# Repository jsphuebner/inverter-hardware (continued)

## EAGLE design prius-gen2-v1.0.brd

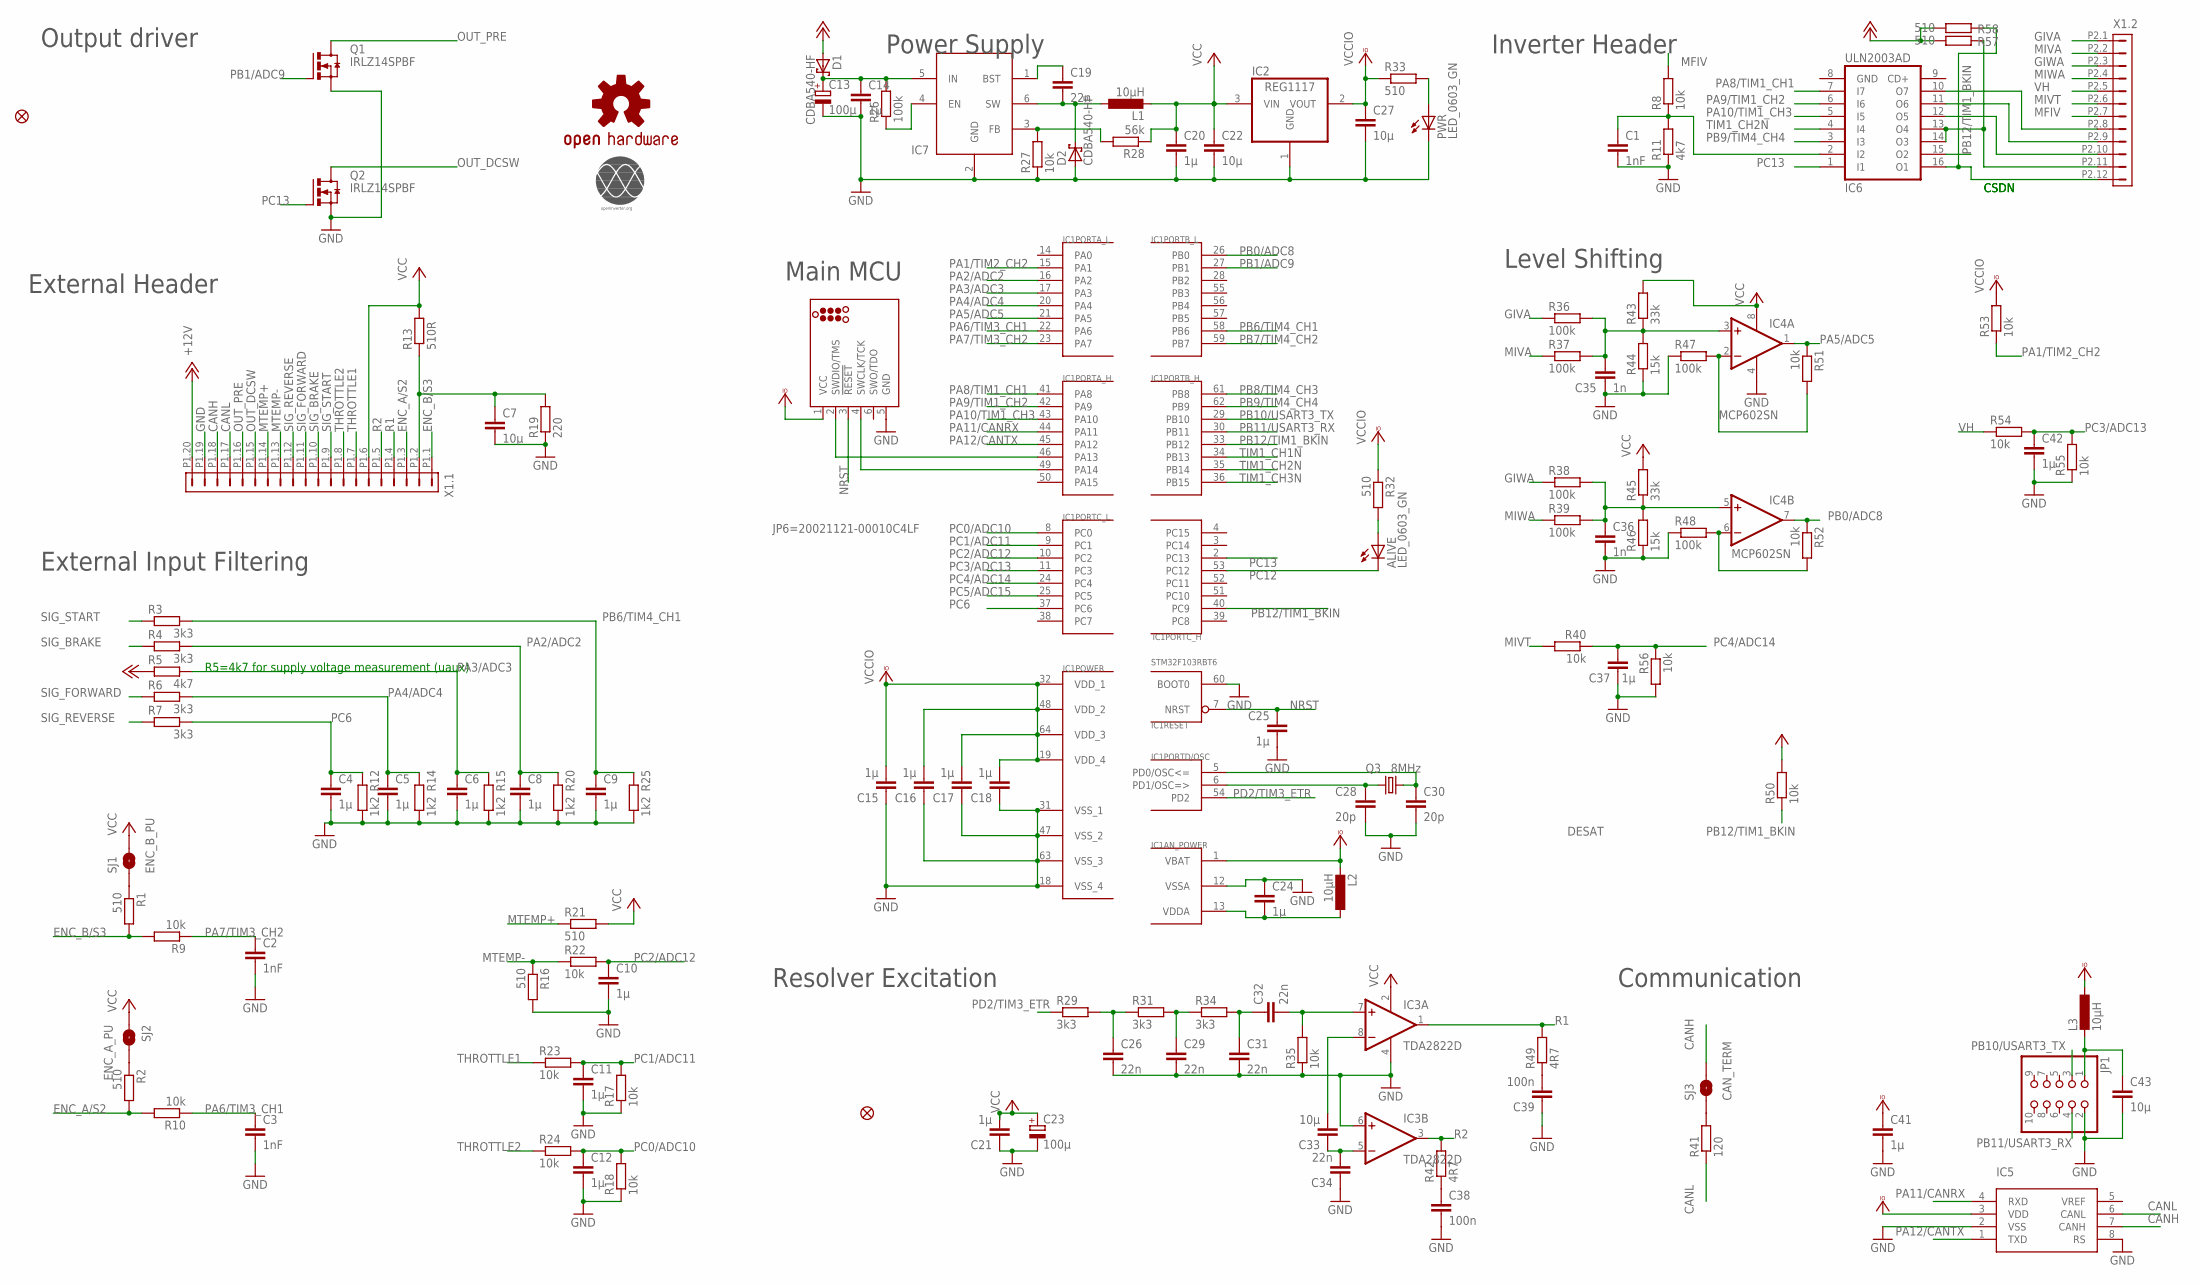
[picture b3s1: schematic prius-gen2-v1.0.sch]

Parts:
ALIVE: LED_0603_GN; SML0805
C1, C2, C3: 1nF; C0603
C4, C5, C6, C8, C9, C10, C11, C12, C14, C15, C16, C17, C18, C20, C21, C24, C25, C37, C41, C42: 1µ; C0603
C7, C22, C27, C33, C43: 10µ; C0805
C13, C23: 100µ; UD-6,3X7,7_NICHICON
C19, C26, C29, C31, C32, C34: 22n; C0603
C28, C30: 20p; C0603
C35, C36: 1n; C0603
C38, C39: 100n; C0603
D1, D2: CDBA540-HF; SMB
FID1, FID2: FIDUCIAL1X2.5; FIDUCIAL-1X2.5
IC1: STM32F103RBT6; TQFP64
IC2: REG1117; SOT223
IC3: TDA2822D; SO08
IC4: MCP602SN; SO08
IC5: SN65HVD230; SO08
IC6: ULN2003AD; SO16
IC7: MB2359DJ; SOT23-6
J1: TC2030_SWD-MCP; TC2030-MCP
JP1: PINHD-2X5/90; 2X05/90
L1: 10µH; L2825P
L2, L3: 10µH; L2012C
LOGO1: OSHW-LOGOM; OSHW-LOGO-M
PWR: LED_0603_GN; SML0805
Q1, Q2: IRLZ14SPBF; D-PAK_TO252AA
Q3: 8MHz; CRYSTAL-TXC-7A
R1, R2, R16, R21, R32, R33, R57, R58: 510; R0603
R3, R4, R6, R7, R29, R31, R34: 3k3; R0603
R5, R11: 4k7; R0603
R8, R9, R10, R17, R18, R22, R23, R24, R27, R35, R40, R50, R51, R52, R53, R54, R55, R56: 10k; R0603
R12, R14, R15, R20, R25: 1k2; R0603
R13: 510R; R0603
R19: 220; R0603
R26, R36, R37, R38, R39, R47, R48: 100k; R0603
R28: 56k; R0603
R41: 120; R0603
R42, R49: 4R7; R0603
R43, R45: 33k; R0603
R44, R46: 15k; R0603
SJ1: ENC_B_PU; SJ_2S-NO
SJ2: ENC_A_PU; SJ_2S-NO
SJ3: CAN_TERM; SJ_2S-NO
U$1: OI-LOGO; OI_LOGO
X1: 5810132011

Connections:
+12V: D1.A, R5.1, R57.1, R58.1, X1.P1.20 (20)
CANH: IC5.7 (CANH), SJ3.2, X1.P1.18 (18)
CANL: IC5.6 (CANL), R41.1, X1.P1.17 (17)
ENC_A/S2: R2.2, R10.2, X1.P1.3 (3)
ENC_B/S3: R1.2, R9.2, X1.P1.1 (1)
GIVA: R36.1, X1.P2.1 (1)
GIWA: R38.1, X1.P2.3 (3)
GND: C1.2, C2.2, C3.2, C4.2, C5.2, C6.2, C7.2, C8.2, C9.2, C10.2, C11.2, C12.2, C13.-, C14.2, C15.1, C16.1, C17.1, C18.1, C20.2, C21.1, C22.2, C23.-, C24.1, C25.2, C26.2, C27.2, C28.2, C29.2, C30.2, C31.2, C34.1, C35.2, C36.2, C37.2, C38.2, C39.1, C41.2, C42.2, C43.2, D2.A, IC1.12 (VSSA), IC1.18 (VSS_4), IC1.31 (VSS_1), IC1.47 (VSS_2), IC1.60 (BOOT0), IC1.63 (VSS_3), IC2.1 (GND), IC3.4 (V-), IC3.6 (+IN), IC4.4 (V-), IC5.2 (VSS), IC5.8 (RS), IC6.8 (GND), IC7.2 (GND), J1.5 (GND), JP1.2, PWR.C, Q1.3 (S), Q2.3 (S), R11.1, R12.1, R14.1, R15.1, R16.2, R17.1, R18.1, R19.1, R20.1, R25.1, R27.1, R35.1, R44.1, R46.1, R47.1, R48.1, R55.1, R56.2, X1.P1.19 (19)
MFIV: R8.2, X1.P2.7 (7)
MIVA: R37.1, X1.P2.2 (2)
MIVT: R40.2, X1.P2.6 (6)
MIWA: R39.1, X1.P2.4 (4)
MTEMP+: R21.1, X1.P1.14 (14)
MTEMP-: R16.1, R22.1, X1.P1.13 (13)
unnamed: IC6.12 (O5), X1.P2.10 (10)
unnamed: C28.1, IC1.6 (PD1/OSC=>), Q3.P$1 (1)
unnamed: C13.+, C14.1, D1.C, IC7.5 (IN), R26.2
unnamed: C30.1, IC1.5 (PD0/OSC<=), Q3.P$2 (2)
unnamed: C19.1, IC7.1 (BST)
unnamed: IC1.46 (PA13), J1.2 (SWDIO/TMS)
unnamed: C24.2, IC1.13 (VDDA), L2.1
unnamed: IC7.4 (EN), R26.1
unnamed: IC1.49 (PA14), J1.4 (SWCLK/TCK)
unnamed: C33.1, C34.2, IC3.5 (-IN)
unnamed: C39.2, R49.1
unnamed: C33.2, IC3.8 (-IN)
unnamed: IC7.3 (FB), R27.2, R28.2
unnamed: C19.2, D2.C, IC7.6 (SW), L1.1
unnamed: IC6.11 (O6), X1.P2.9 (9)
unnamed: IC6.10 (O7), X1.P2.8 (8)
unnamed: C29.1, R31.2, R34.1
unnamed: C31.1, C32.1, R34.2
unnamed: C32.2, IC3.7 (+IN), R35.2
unnamed: R2.1, SJ2.2
unnamed: R1.1, SJ1.1
unnamed: PWR.A, R33.2
unnamed: ALIVE.A, R32.2
unnamed: C1.1, IC6.2 (I2), R8.1, R11.2
unnamed: IC6.16 (O1), R58.2, X1.P2.12 (12)
unnamed: R41.2, SJ3.1
unnamed: C38.1, R42.1
unnamed: C43.1, JP1.1, L3.2
unnamed: IC6.13 (O4), IC6.14 (O3), R57.2, X1.P2.11 (11)
unnamed: C26.1, R29.2, R31.1
unnamed: C36.1, IC4.5 (+IN), R38.2, R39.2, R45.1, R46.2
unnamed: C35.1, IC4.3 (+IN), R36.2, R37.2, R43.1, R44.2
unnamed: IC4.2 (-IN), R47.2, R51.2
unnamed: IC4.6 (-IN), R48.2, R52.2
NRST: C25.1, IC1.7 (NRST), J1.3 (!RESET)
OUT_DCSW: Q2.4 (D), X1.P1.15 (15)
OUT_PRE: Q1.4 (D), X1.P1.16 (16)
PA1/TIM2_CH2: IC1.15 (PA1), R53.1
PA2/ADC2: C8.1, IC1.16 (PA2), R4.2, R20.2
PA3/ADC3: C6.1, IC1.17 (PA3), R5.2, R15.2
PA4/ADC4: C5.1, IC1.20 (PA4), R6.2, R14.2
PA5/ADC5: IC1.21 (PA5), IC4.1 (OUT), R51.1
PA6/TIM3_CH1: C3.1, IC1.22 (PA6), R10.1
PA7/TIM3_CH2: C2.1, IC1.23 (PA7), R9.1
PA8/TIM1_CH1: IC1.41 (PA8), IC6.7 (I7)
PA9/TIM1_CH2: IC1.42 (PA9), IC6.6 (I6)
PA10/TIM1_CH3: IC1.43 (PA10), IC6.5 (I5)
PA11/CANRX: IC1.44 (PA11), IC5.4 (RXD)
PA12/CANTX: IC1.45 (PA12), IC5.1 (TXD)
PB0/ADC8: IC1.26 (PB0), IC4.7 (OUT), R52.1
PB1/ADC9: IC1.27 (PB1), Q1.1 (G)
PB6/TIM4_CH1: C9.1, IC1.58 (PB6), R3.2, R25.2
PB7/TIM4_CH2: IC1.59 (PB7)
PB8/TIM4_CH3: IC1.61 (PB8)
PB9/TIM4_CH4: IC1.62 (PB9), IC6.3 (I3)
PB10/USART3_TX: IC1.29 (PB10), JP1.3
PB11/USART3_RX: IC1.30 (PB11), JP1.4
PB12/TIM1_BKIN: IC1.33 (PB12), IC1.40 (PC9), IC6.15 (O2), R50.1
PC0/ADC10: C12.1, IC1.8 (PC0), R18.2, R24.2
PC1/ADC11: C11.1, IC1.9 (PC1), R17.2, R23.2
PC2/ADC12: C10.1, IC1.10 (PC2), R22.2
PC3/ADC13: C42.1, IC1.11 (PC3), R54.2, R55.2
PC4/ADC14: C37.1, IC1.24 (PC4), R40.1, R56.1
PC5/ADC15: IC1.25 (PC5)
PC6: C4.1, IC1.37 (PC6), R7.2, R12.2
PC12: ALIVE.C, IC1.53 (PC12)
PC13: IC1.2 (PC13), IC6.1 (I1), Q2.1 (G)
PD2/TIM3_ETR: IC1.54 (PD2), R29.1
R1: IC3.1 (OUT), R49.2, X1.P1.4 (4)
R2: IC3.3 (OUT), R42.2, X1.P1.5 (5)
S4/S1: C7.1, R13.1, R19.2, X1.P1.2 (2)
SIG_BRAKE: R4.1, X1.P1.10 (10)
SIG_FORWARD: R6.1, X1.P1.11 (11)
SIG_REVERSE: R7.1, X1.P1.12 (12)
SIG_START: R3.1, X1.P1.9 (9)
THROTTLE1: R23.1, X1.P1.7 (7)
THROTTLE2: R24.1, X1.P1.8 (8)
TIM1_CH1N: IC1.34 (PB13)
TIM1_CH2N: IC1.35 (PB14), IC6.4 (I4)
TIM1_CH3N: IC1.36 (PB15)
VCC: C20.1, C21.2, C22.1, C23.+, IC2.3 (VIN), IC3.2 (V+), IC4.8 (V+), L1.2, R13.2, R21.2, R28.1, R43.2, R45.2, R50.2, SJ1.2, SJ2.1, X1.P1.6 (6)
VCCIO: C15.2, C16.2, C17.2, C18.2, C27.1, C41.1, IC1.1 (VBAT), IC1.19 (VDD_4), IC1.32 (VDD_1), IC1.48 (VDD_2), IC1.64 (VDD_3), IC2.2 (VOUT), IC5.3 (VDD), J1.1 (VCC), L2.2, L3.1, R32.1, R33.1, R53.2
VH: R54.1, X1.P2.5 (5)

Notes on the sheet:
Output driver
Resolver Excitation
External Input Filtering
External Header
Communication
Power Supply
Inverter Header
Level Shifting
Main MCU
R5=4k7 for supply voltage measurement (uaux)
JP6=20021121-00010C4LF
DESAT
IC7
IC5
CSDN

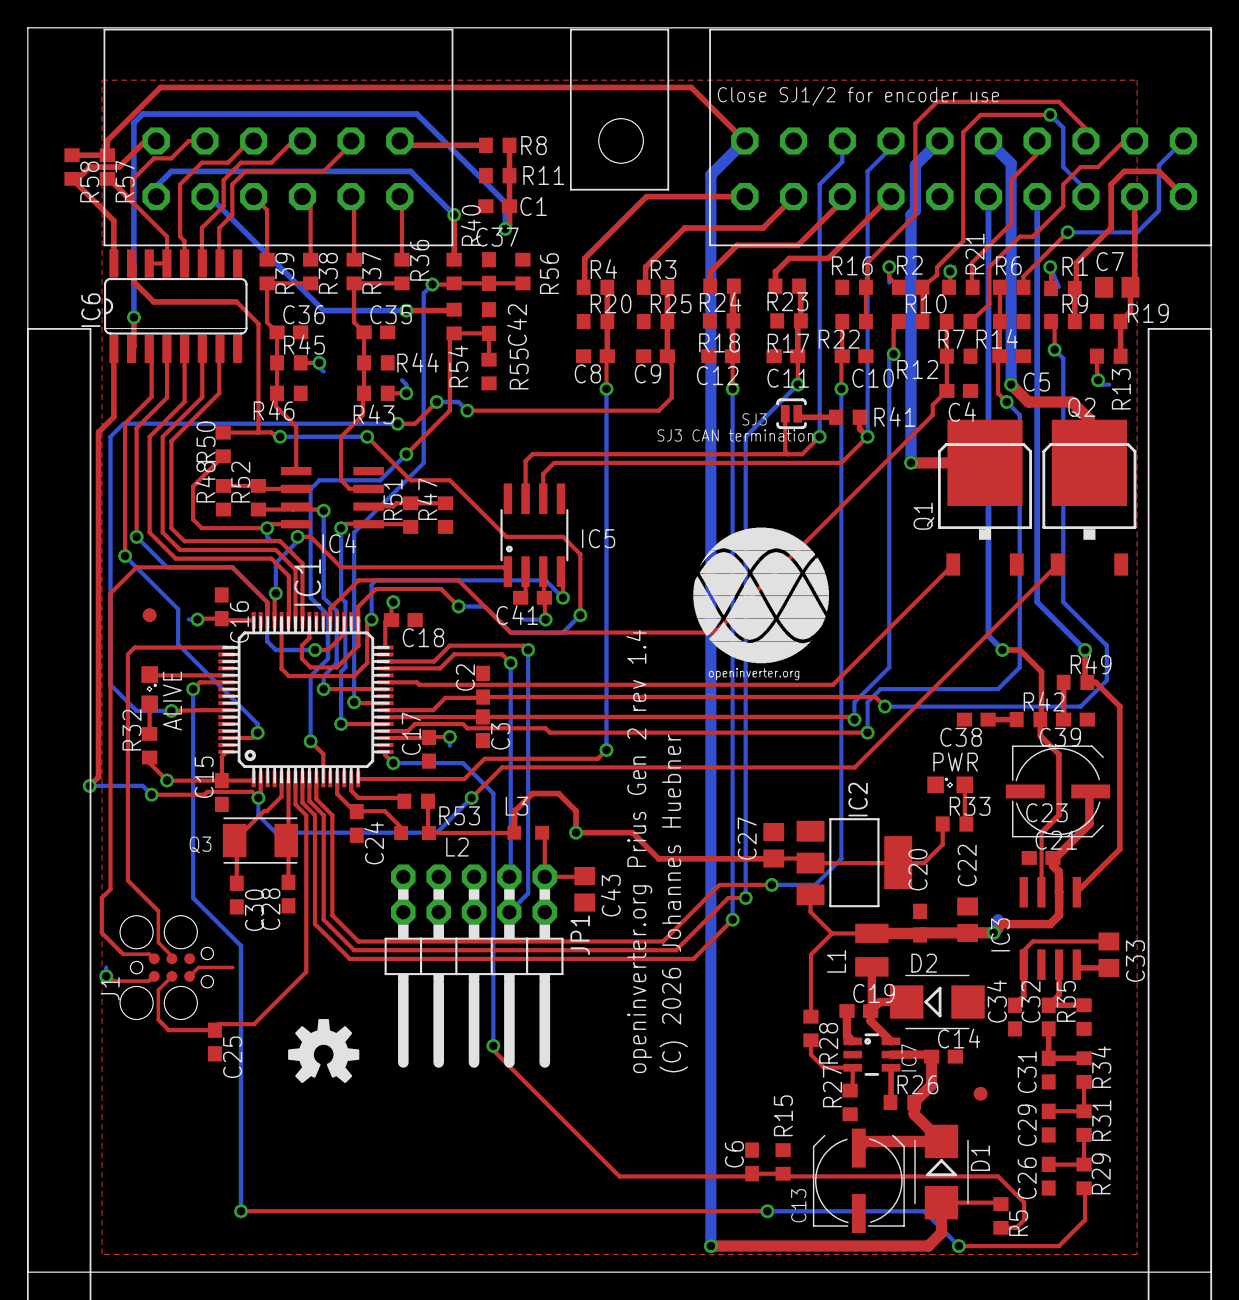
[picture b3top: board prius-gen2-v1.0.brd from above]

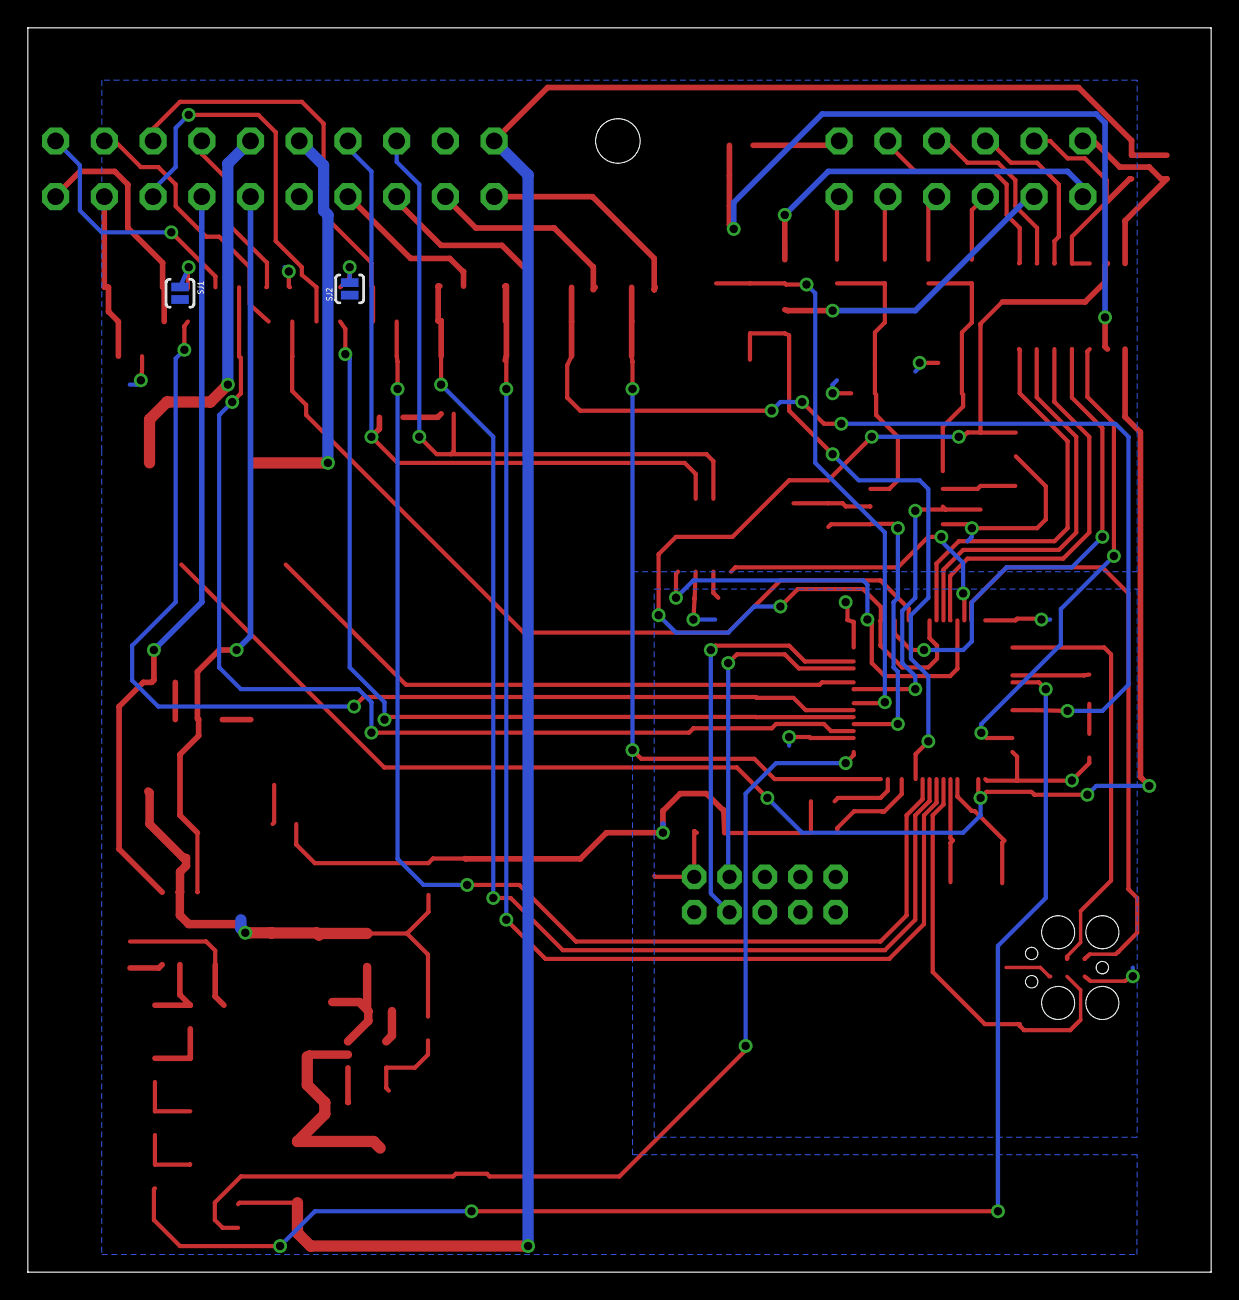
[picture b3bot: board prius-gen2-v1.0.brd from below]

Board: 2 copper layers, 85.0 x 89.4 mm, 126 parts (2 on the bottom side), 92 nets.

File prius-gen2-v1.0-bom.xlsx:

Designator | Comment | Package | LCSC Part #
ALIVE, PWR | LED_0603_GN | CHIPLED-0805 | C84256
C7, C22, C27, C33, C43 | 10uF | C0805 | C15850
C1, C2, C3, C35, C36 | 1nF | C0603 | C46653
C13, C23 | 100uF | SMD-ECAP-6.3X7.7 | C176675 | e
C28, C30 | 22p | C0603 | C1804
C4, C5, C6, C8, C9, C10, C11, C12, C14, C15, C16, C17, C18, C20, C21, C24, C25,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 | 1uF | C0603 | C28323
C19, C26, C29, C31, C32, C34 | 22n | C0603 | C21122
D1, D2 | CDBA540-HF | SMB | C22452
IC7 | MP2359DJ-LF-Z | TSOT-23-6 | C14259
IC3 | TDA2822D | SO08 | C73296 | e
IC5 | SN65HVD230 | SO08 | C12084
IC1 | STM32F103RBT6 | LQFP-64_10.0x10.0x0.5P | C8735
IC6 | ULN2003AD | SO16 | C7512
IC4 | MCP6002T-I/SN | SO08 | C7377
IC2 | AMS1117-3.3 | SOT-223 | C6186
L2, L3 | 10uH | L0805 | C1046
L1 | 6.8uH | L1210 | C87559 | e
Q3 | 8MHz | SMD-5032_2P | C115962
R19 | 220Ω | R0603 | C22962
R12, R14, R15, R20, R25 | 1.2KΩ | R0603 | C22765
R1, R2, R13, R16, R21, R32, R33 | 510Ω | R0603 | C23193
R8, R9, R10, R17, R18, R22, R23, R24, R27, R30, R35, R40, R50, R51, R52, R53, R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 | 10KΩ | R0603 | C17414
R3, R4, R6, R7, R29, R31, R34 | 3.3KΩ | R0603 | C26010
R5, R11 | 4.7KΩ | R0603 | C17673
R42, R49 | 4.7Ω | R0603 | C23164
R26, R36, R37, R38, R39, R47, R48 | 100kΩ | R0603 | C25803
R28 | 56kΩ | R0603 | C23206
Q1, Q2 | AP9T18GH-HF | TO-252-2 | C124546 | e
C38, C39 | 100nF | C0603 | C14663
R44, R46 | 15kΩ | R0603 | C22809
R43, R45 | 33kΩ | R0603 | C4216
R41 | 120Ω | R0603 | C22787

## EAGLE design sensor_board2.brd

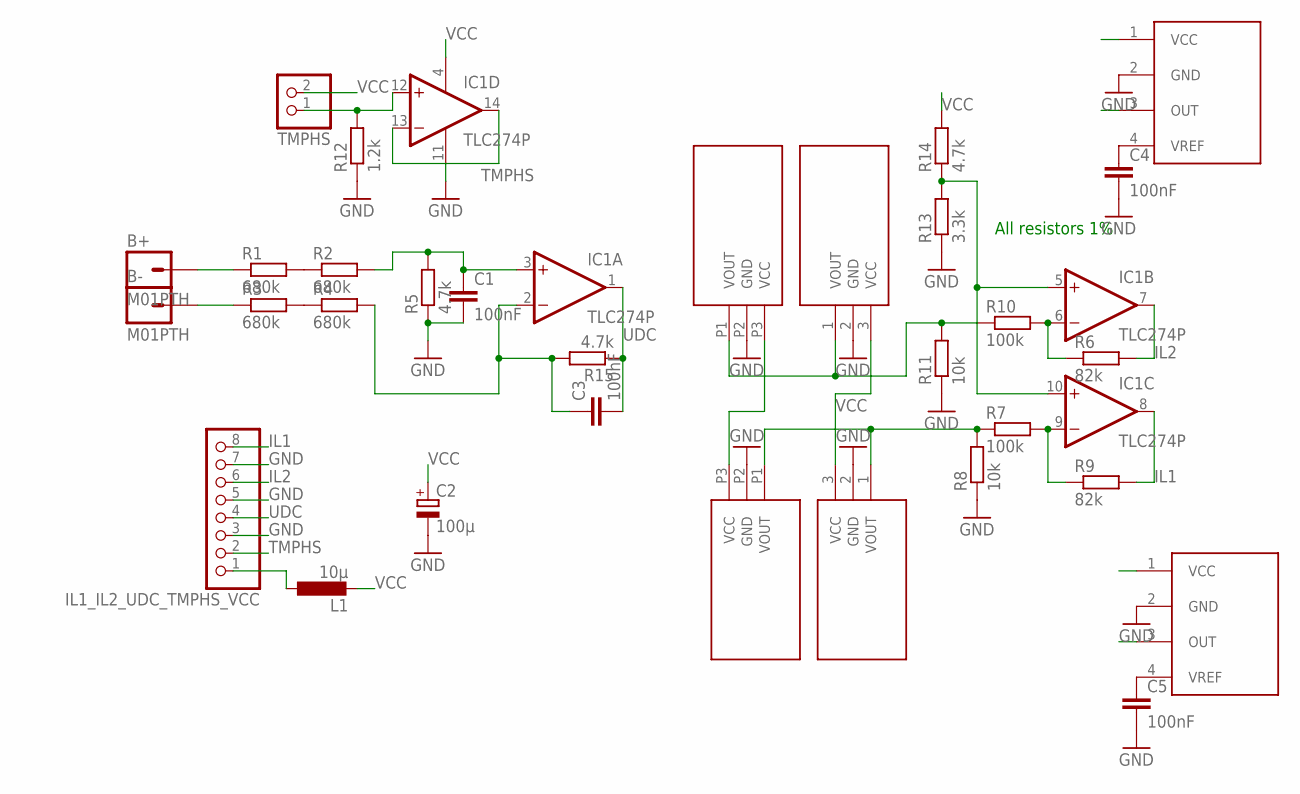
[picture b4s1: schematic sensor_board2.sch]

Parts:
B+: M01PTH; 1X01
B-: M01PTH; 1X01
C1, C3, C4, C5: 100nF; C025-024X044
C2: 100µ; E2,5-6E
IC1: TLC274P; DIL14
IL1_IL2_UDC_TMPHS_VCC: PINHD-1X8; 1X08
L1: 10µ; 0207/12
R1, R2, R3, R4: 680k; 0207/10
R5, R14, R15: 4.7k; 0207/10
R6, R9: 82k; 0207/10
R7, R10: 100k; 0207/10
R8, R11: 10k; 0207/10
R12: 1.2k; 0207/10
R13: 3.3k; 0207/10
TMPHS: PINHD-1X2; 1X02
U$1, U$2: TAMURA_L01Z_S05
U$3, U$4: HTFS
U$5, U$6: TAMURA_L06P_S05L06P; TAMURA_L06P_S05

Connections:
GND: C1.2, C2.-, C4.2, C5.2, IC1.11 (V-), IL1_IL2_UDC_TMPHS_VCC.3, IL1_IL2_UDC_TMPHS_VCC.5, IL1_IL2_UDC_TMPHS_VCC.7, R5.1, R8.1, R11.1, R12.1, R13.1, U$1.2 (GND), U$2.2 (GND), U$3.2 (GND), U$4.2 (GND), U$5.P2 (GND), U$6.P2 (GND)
IL1: IC1.8 (OUT), IL1_IL2_UDC_TMPHS_VCC.8, R9.2
IL2: IC1.7 (OUT), IL1_IL2_UDC_TMPHS_VCC.6, R6.2
unnamed: R1.2, R2.1
unnamed: R3.2, R4.1
unnamed: IC1.5 (+IN), IC1.10 (+IN), R13.2, R14.1
unnamed: C1.1, IC1.3 (+IN), R2.2, R5.2
unnamed: B+.1, R1.1
unnamed: B-.1, R3.1
unnamed: IL1_IL2_UDC_TMPHS_VCC.1, L1.1
unnamed: IC1.9 (-IN), R7.2, R9.1
unnamed: IC1.6 (-IN), R6.1, R10.2
unnamed: C3.1, IC1.2 (-IN), R4.2, R15.2
unnamed: C4.1, U$3.4 (VREF)
unnamed: C5.1, U$4.4 (VREF)
unnamed: IC1.12 (+IN), R12.2, TMPHS.1
TMPHS: IC1.13 (-IN), IC1.14 (OUT), IL1_IL2_UDC_TMPHS_VCC.2
UDC: C3.2, IC1.1 (OUT), IL1_IL2_UDC_TMPHS_VCC.4, R15.1
VCC: C2.+, IC1.4 (V+), L1.2, R14.2, TMPHS.2, U$1.3 (VCC), U$2.3 (VCC), U$3.1 (VCC), U$4.1 (VCC), U$5.P3 (VCC), U$6.P3 (VCC)
VOUT1: R7.1, R8.2, U$2.1 (VOUT), U$4.3 (OUT), U$6.P1 (VOUT)
VOUT2: R10.1, R11.2, U$1.1 (VOUT), U$3.3 (OUT), U$5.P1 (VOUT)

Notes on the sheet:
All resistors 1%

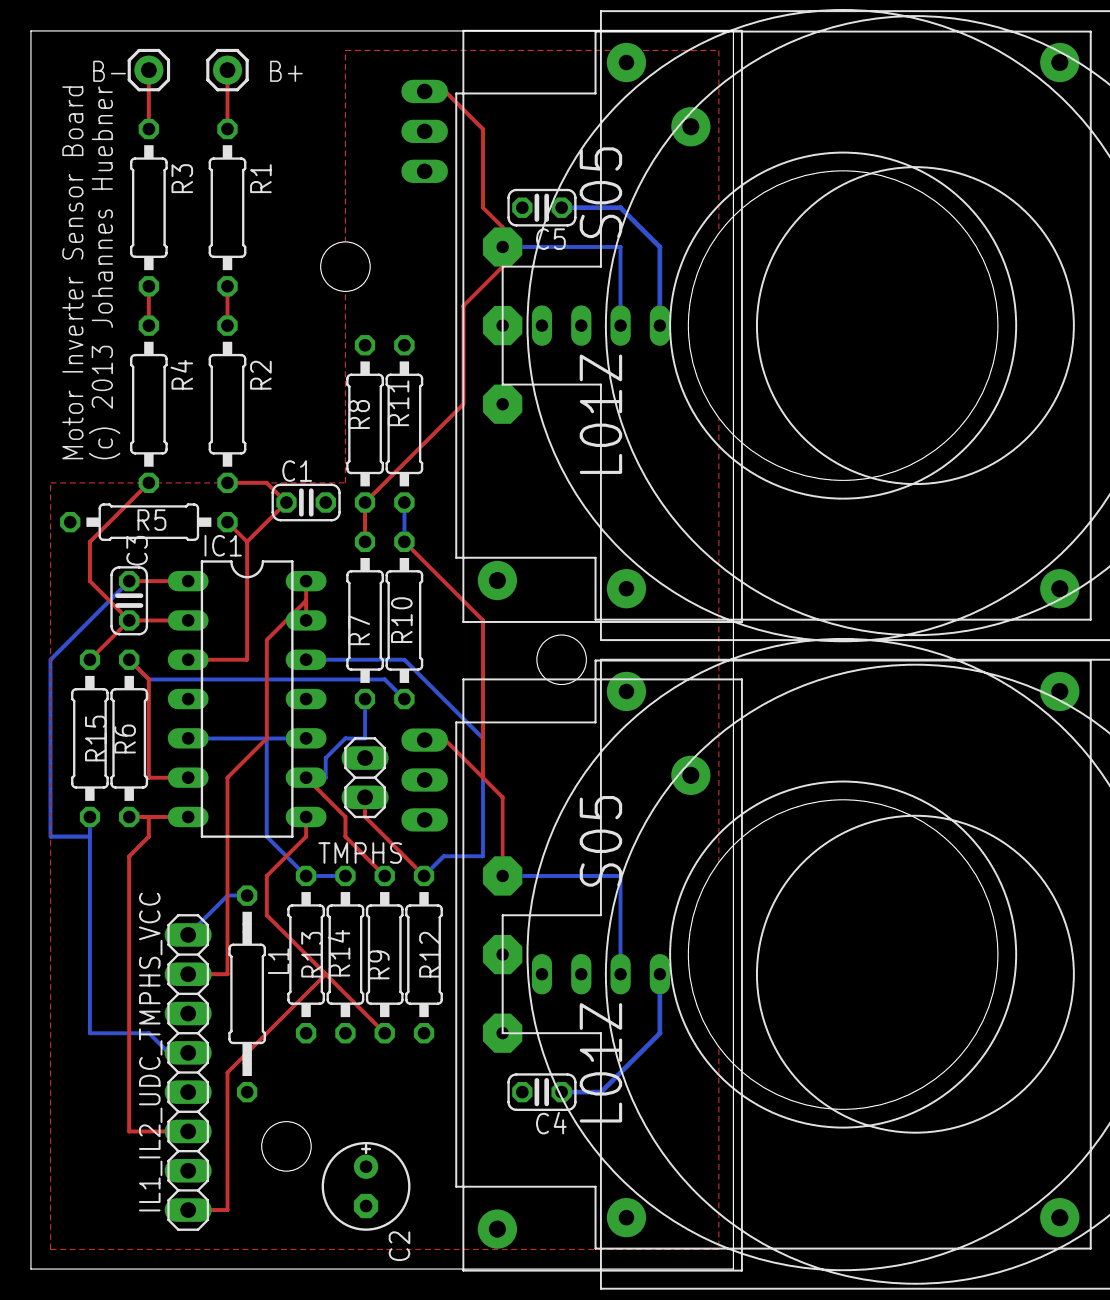
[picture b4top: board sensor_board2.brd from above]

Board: 2 copper layers, 45.4 x 80.0 mm, 32 parts (0 on the bottom side), 21 nets.

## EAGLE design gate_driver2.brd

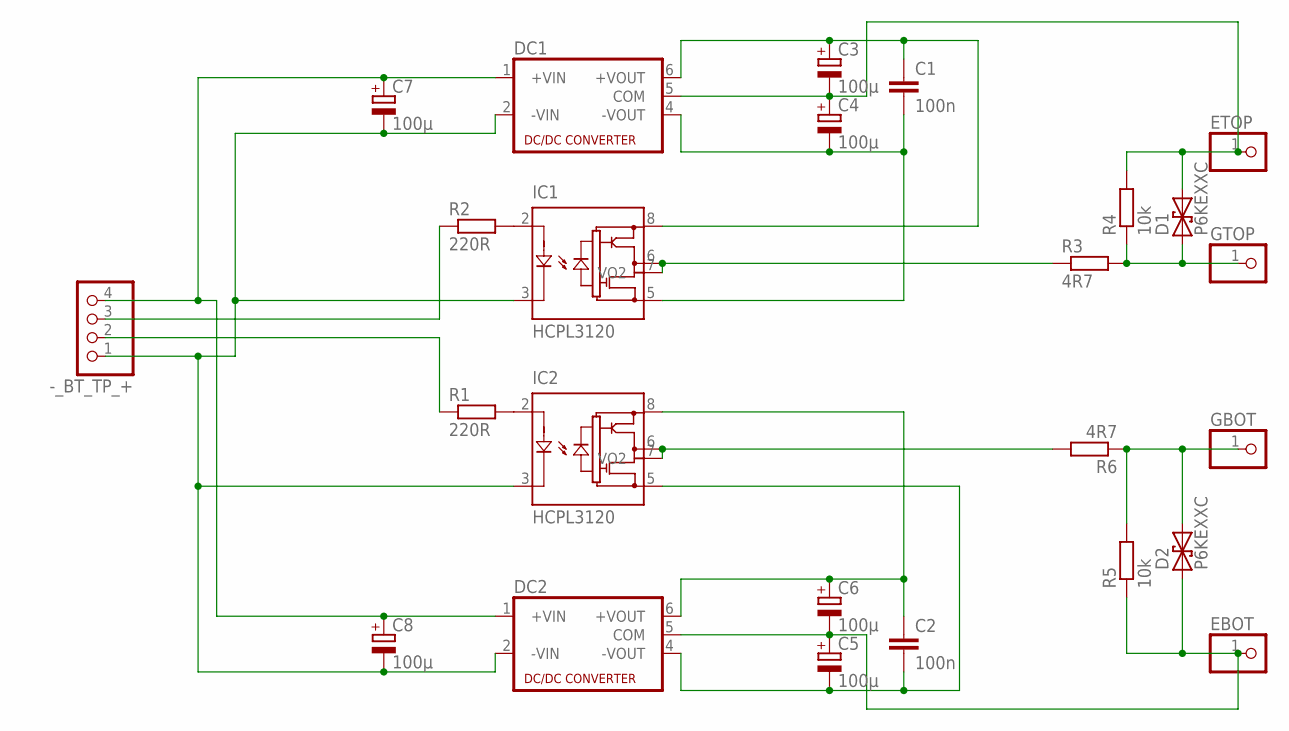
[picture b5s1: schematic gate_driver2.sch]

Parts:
-_BT_TP_+: PINHD-1X4; 1X04
C1, C2: 100n; C050-025X075
C3, C4, C5, C6: 100µ; E2,5-6E
C7, C8: 100µ; E2,5-5
D1, D2: P6KEXXC; CB417-15
DC1, DC2: NMA
EBOT: PINHD-1X1; 1X01
ETOP: PINHD-1X1; 1X01
GBOT: PINHD-1X1; 1X01
GTOP: PINHD-1X1; 1X01
IC1, IC2: HCPL3120; DIL08
R1, R2: 220R; 0207/10
R3, R6: 4R7; 0309/12
R4, R5: 10k; 0207/10

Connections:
EBOT: C5.+, C6.-, D2.A (1), DC2.5 (COM), EBOT.1, R5.1
ETOP: C3.-, C4.+, D1.C (2), DC1.5 (COM), ETOP.1, R4.2
GBOT: D2.C (2), GBOT.1, R5.2, R6.1
GND: -_BT_TP_+.1, C7.-, C8.-, DC1.2 (-VIN), DC2.2 (-VIN), IC1.3 (CATHODE), IC2.3 (CATHODE)
GTOP: D1.A (1), GTOP.1, R3.2, R4.1
unnamed: IC2.2 (ANODE), R1.2
unnamed: IC1.2 (ANODE), R2.2
unnamed: C1.2, C4.-, DC1.4 (-VOUT), IC1.5 (VEE)
unnamed: C1.1, C3.+, DC1.6 (+VOUT), IC1.8 (VCC)
unnamed: C2.1, C6.+, DC2.6 (+VOUT), IC2.8 (VCC)
unnamed: C2.2, C5.-, DC2.4 (-VOUT), IC2.5 (VEE)
unnamed: IC1.6 (VO), IC1.7 (VO2), R3.1
unnamed: IC2.6 (VO), IC2.7 (VO2), R6.2
unnamed: -_BT_TP_+.4, C7.+, C8.+, DC1.1 (+VIN), DC2.1 (+VIN)
unnamed: -_BT_TP_+.3, R2.1
unnamed: -_BT_TP_+.2, R1.1

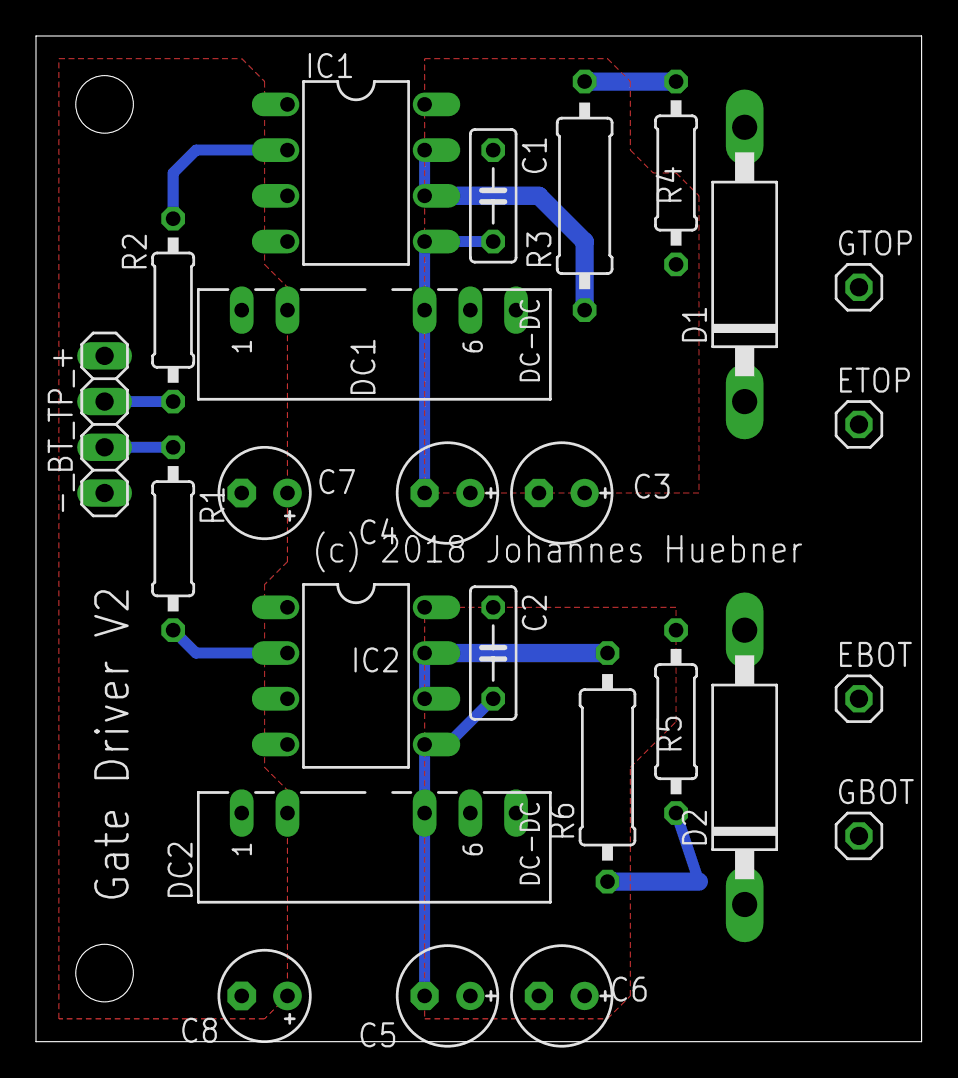
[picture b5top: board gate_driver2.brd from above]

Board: 2 copper layers, 49.2 x 55.9 mm, 25 parts (0 on the bottom side), 16 nets.

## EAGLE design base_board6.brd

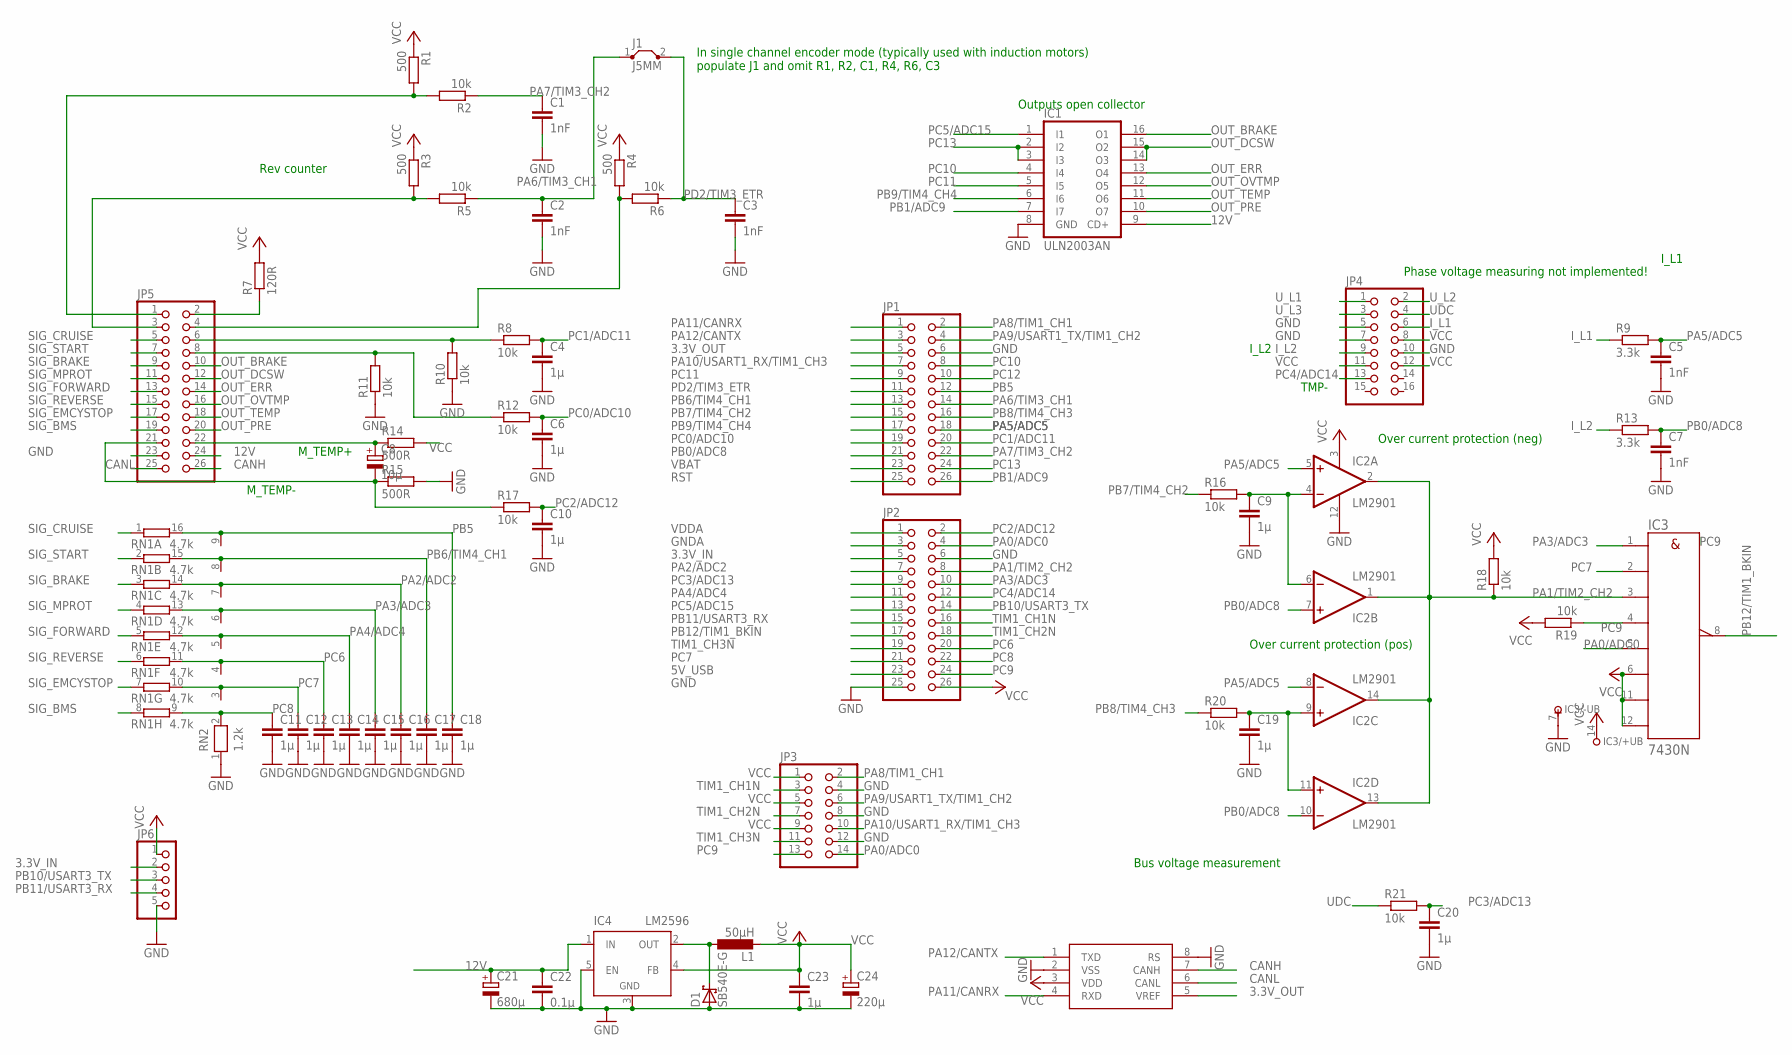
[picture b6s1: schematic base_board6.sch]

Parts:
C1, C2, C3, C5, C7: 1nF; C025-024X044
C4, C6, C9, C10, C11, C12, C13, C14, C15, C16, C17, C18, C19, C20, C23: 1µ; C025-024X044
C8: 10µ; E2-4
C21: 680µ; E2,5-5
C22: 0.1µ; C050-024X044
C24: 220µ; E2-4
D1: SB540E-G; DO201T15
IC1: ULN2003AN; DIL16
IC2: LM2901; DIL14
IC3: 7430N; DIL14
IC4: LM2596; TO220-51
IC5: MCP2562P; DIL08
J1: J5MM; 05
JP1, JP2, JP5: PINHD-2X13; 2X13
JP3: PINHD-2X7; 2X07
JP4: PINHD-2X8; 2X08
JP6: PINHD-1X5; 1X05
L1: 50µH; TJ3-U1
R1, R3, R4: 500; 0207/10
R2, R5, R6, R8, R10, R11, R12, R16, R17, R18, R19, R20, R21: 10k; 0207/10
R7: 120R; 0207/10
R9, R13: 3.3k; 0207/10
R14, R15: 500R; 0207/10
RN1: 4.7k; DIL16
RN2: 1.2k; RN-9

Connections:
3.3V_IN: JP2.5, JP6.2
3.3V_OUT: IC5.5 (VREF), JP1.5
5V_USB: JP2.23
12V: C21.+, C22.1, IC1.9 (CD+), IC4.1 (IN), JP5.24
CANH: IC5.7 (CANH), JP5.26
CANL: IC5.6 (CANL), JP5.25
GND: C1.2, C2.2, C3.2, C4.2, C5.2, C6.2, C7.2, C9.2, C10.2, C11.2, C12.2, C13.2, C14.2, C15.2, C16.2, C17.2, C18.2, C19.2, C20.2, C21.-, C22.2, C23.2, C24.-, D1.A, IC1.8 (GND), IC2.12 (GND), IC3.7 (-UB), IC4.3 (GND), IC4.5 (EN), IC5.2 (VSS), IC5.8 (RS), JP1.6, JP2.6, JP2.25, JP3.4, JP3.8, JP3.12, JP4.5, JP4.7, JP4.10, JP5.23, JP6.5, R10.1, R11.1, R15.2, RN2.1
GNDA: JP2.3
I_L1: JP4.6, R9.1
I_L2: JP4.9, R13.1
unnamed: JP5.2, R7.1
unnamed: JP5.3, R3.2, R5.2
unnamed: JP5.1, R1.2, R2.2
unnamed: C19.1, IC2.9 (+IN), IC2.11 (+IN), R20.2
unnamed: JP5.4, R4.2, R6.2
unnamed: C8.+, JP5.22, R14.1
unnamed: D1.C, IC4.2 (OUT), L1.1
unnamed: C9.1, IC2.4 (-IN), IC2.6 (-IN), R16.2
unnamed: C8.-, JP5.21, R15.1, R17.1
OUT_BRAKE: IC1.16 (O1), JP5.10
OUT_DCSW: IC1.14 (O3), IC1.15 (O2), JP5.12
OUT_ERR: IC1.13 (O4), JP5.14
OUT_OVTMP: IC1.12 (O5), JP5.16
OUT_PRE: IC1.10 (O7), JP5.20
OUT_TEMP: IC1.11 (O6), JP5.18
PA0/ADC0: IC3.5 (E), JP2.4, JP3.14
PA1/TIM2_CH2: IC2.1 (OUT), IC2.2 (OUT), IC2.13 (OUT), IC2.14 (OUT), IC3.3 (C), JP2.8, R18.1
PA2/ADC2: C16.1, JP2.7, RN1.14 (2), RN2.7
PA3/ADC3: C15.1, IC3.1 (A), JP2.10, RN1.13 (2), RN2.6
PA4/ADC4: C14.1, JP2.11, RN1.12 (2), RN2.5
PA5/ADC5: C5.1, IC2.5 (+IN), IC2.8 (-IN), JP1.18, R9.2
PA6/TIM3_CH1: C2.1, J1.1, JP1.14, R5.1
PA7/TIM3_CH2: C1.1, JP1.22, R2.1
PA8/TIM1_CH1: JP1.2, JP3.2
PA9/USART1_TX/TIM1_CH2: JP1.4, JP3.6
PA10/USART1_RX/TIM1_CH3: JP1.7, JP3.10
PA11/CANRX: IC5.4 (RXD), JP1.1
PA12/CANTX: IC5.1 (TXD), JP1.3
PB0/ADC8: C7.1, IC2.7 (+IN), IC2.10 (-IN), JP1.21, R13.2
PB1/ADC9: IC1.7 (I7), JP1.26
PB5: C18.1, JP1.12, RN1.16 (2), RN2.9
PB6/TIM4_CH1: C17.1, JP1.13, RN1.15 (2), RN2.8
PB7/TIM4_CH2: JP1.15, R16.1
PB8/TIM4_CH3: JP1.16, R20.1
PB9/TIM4_CH4: IC1.6 (I6), JP1.17
PB10/USART3_TX: JP2.14, JP6.3
PB11/USART3_RX: JP2.15, JP6.4
PB12/TIM1_BKIN: IC3.8 (Y), JP2.17
PC0/ADC10: C6.1, JP1.19, R12.2
PC1/ADC11: C4.1, JP1.20, R8.2
PC2/ADC12: C10.1, JP2.2, R17.2
PC3/ADC13: C20.1, JP2.9, R21.2
PC4/ADC14: JP2.12, JP4.13
PC5/ADC15: IC1.1 (I1), JP2.13
PC6: C13.1, JP2.20, RN1.11 (2), RN2.4
PC7: C12.1, IC3.2 (B), JP2.21, RN1.10 (2), RN2.3
PC8: C11.1, JP2.22, RN1.9 (2), RN2.2
PC9: IC3.4 (D), JP2.24, JP3.13, R19.1
PC10: IC1.4 (I4), JP1.8
PC11: IC1.5 (I5), JP1.9
PC12: JP1.10
PC13: IC1.2 (I2), IC1.3 (I3), JP1.24
PD2/TIM3_ETR: C3.1, J1.2, JP1.11, R6.1
RST: JP1.25
SIG_BMS: JP5.19, RN1.8 (1)
SIG_BRAKE: JP5.9, RN1.3 (1)
SIG_CRUISE: JP5.5, RN1.1
SIG_EMCYSTOP: JP5.17, RN1.7 (1)
SIG_FORWARD: JP5.13, RN1.5 (1)
SIG_MPROT: JP5.11, RN1.4 (1)
SIG_REVERSE: JP5.15, RN1.6 (1)
SIG_START: JP5.7, RN1.2 (1)
TIM1_CH1N: JP2.16, JP3.3
TIM1_CH2N: JP2.18, JP3.7
TIM1_CH3N: JP2.19, JP3.11
UDC: JP4.4, R21.1
U_L1: JP4.1
U_L2: JP4.2
U_L3: JP4.3
VBAT: JP1.23
VCC: C23.1, C24.+, IC2.3 (V+), IC3.6 (F), IC3.11 (G), IC3.12 (H), IC3.14 (+UB), IC4.4 (FB), IC5.3 (VDD), JP2.26, JP3.1, JP3.5, JP3.9, JP4.8, JP4.11, JP4.12, JP6.1, L1.2, R1.1, R3.1, R4.1, R7.2, R14.2, R18.2, R19.2
VDDA: JP2.1
X: JP5.6, R8.1, R10.2
Y: JP5.8, R11.2, R12.1

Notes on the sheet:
M_TEMP+
M_TEMP-
TMP-
Over current protection (pos)
Outputs open collector
Phase voltage measuring not implemented!
Bus voltage measurement
Rev counter
Over current protection (neg)
I_L1
I_L2
In single channel encoder mode (typically used with induction motors) populate J1 and omit R1, R2, C1, R4, R6, C3
